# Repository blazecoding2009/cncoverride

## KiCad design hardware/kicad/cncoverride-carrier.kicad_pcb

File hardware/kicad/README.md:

# CNC Override Pendant PCB · R1

R1 replaces the harness carrier with a **190 × 170 mm direct-mount panel PCB**. The display, four knobs and eight buttons sit on the front. The ESP32-C6-DevKitC-1 and expander mount on the rear. Four Ø3.2 mm holes on a 182 × 162 mm pattern mount the main board. Dimensions and panel clearances are provisional.

| References | Direct assembly |
|---|---|
| ENC1, ENC2 | Bourns PEC11H-4215F-S0024 push encoders for Feed and Spindle. Includes plated slots for the two anchors per encoder. |
| SW1, SW2 | Lorlin CK1049, one-pole PCB rotary switch with break-before-make contacts. Set the stop washers for three and five positions respectively. |
| SW3–SW10 | 1U Cherry MX PCB-mount switches with five pins including the plastic locating pegs. Use labeled keycaps for X/Y, Z, Feed Hold and Cycle Start. |
| J1, H5–H8 | Adafruit 2050 resistive HX8357D TFT breakout, rotated to landscape. Solder a 2.54 mm header to the breakout's JP2 and to the pendant PCB. Use four M2.5 standoffs so the header carries no display mounting load. |
| J2, J3 | Solder the DevKitC's two 16-pin strips directly to the rear. The native USB-C port faces the top edge and goes to the Raspberry Pi. |
| U1 | Rear-mounted MCP23017-E/SP, 7.62 mm DIP-28. A0–A2 are grounded for address 0x20. |

## KiCad project

Open **cncoverride-carrier.kicad_pro** in KiCad 8 or later. The single-sheet schematic and PCB use the included project-local symbols and footprints. The board references are linked to their schematic instances.

## TFT connection

J1 mirrors the physical JP2 hole pattern from the Adafruit 2050 Eagle CAD. The glass faces the controls. The four TFT mounting holes use the 91.44 × 60.96 mm landscape spacing from Adafruit's CAD. Set the TFT's IM2 jumper for SPI before mounting it. Set the display rotation in firmware.

| JP2 pin | Signal |
|---|---|
| 1, 15 | GND |
| 2 | USB 5 V to VIN |
| 4 | TFT SCK |
| 6 | TFT MOSI |
| 7 | TFT CS |
| 8 | TFT D/C |
| 19 | SD CS held high by R4 |
| Other holes | Unassigned |

## Control inputs

| ESP32-C6 GPIO | Function |
|---|---|
| 0 / 1 | Feed encoder A / B |
| 2 / 3 | Spindle encoder A / B |
| 6 / 7 | Expander I²C SDA / SCL |
| 10 / 11 | Feed Hold / Cycle Start |
| 18 / 19 | Z+ / Z− |
| 20 / 21 / 22 / 23 | TFT SCK / MOSI / CS / D/C |

MCP23017 bank A bits 0–6 are X+, X−, Y+, Y−, Feed push, Spindle push, and Rapid 25%. Bank B bits 0–6 are Jog OFF, .001″, .010″, .100″, CONT, Rapid 50%, and Rapid 100%. Enable their pull-ups. GPA7 and GPB7 are reserved because the current datasheet specifies them as output only. Selector common A goes to ground. Rapid uses throws 1–3 for 25%, 50% and 100%. Jog uses throws 1–5 in the order above. In firmware, an open or ambiguous jog selector disarms jogging.

RN1 is an eight-resistor bussed 10 kΩ pull-up network with common on pin 1. R1/R2 are 4.7 kΩ for I²C, R3/R4 are 10 kΩ for expander reset and TFT SD CS. C1 is 100 nF across the expander supply. C2 is 10 µF near the TFT supply. The DevKitC's 3.3 V rail powers the expander. Its 5 V rail supplies TFT VIN. The machine's hardware E-stop uses the machine's documented circuit.

## Job buttons

- **SW9 Feed Hold (GPIO10)** requests a controlled hold. Use CNCjs gcode:pause during a running job so the sender pauses along with Grbl. Feed Hold leaves the spindle running.
- **SW10 Cycle Start (GPIO11)** starts the job already loaded in CNCjs when CNCjs and Grbl are idle. Use gcode:start for a new cycle and gcode:resume to continue a paused job when Grbl is ready. Require a fresh button press and a live controller connection. Suppress Cycle Start while Grbl is jogging, homing, alarmed, or in a door state.

The command behavior is the target for the firmware and Pi bridge. [CNCjs job commands](https://github.com/cncjs/cncjs/blob/v1.11.5/src/server/controllers/Grbl/GrblController.js#L1305-L1359) · [Grbl real-time commands](https://github.com/gnea/grbl/blob/v1.1h.20190825/doc/markdown/commands.md#grbl-v11-realtime-commands)

## Review status

All numbered schematic pins and PCB pads agree, including unused pins. The PCB placement and assigned nets are ready for routing. KiCad ERC/DRC and physical fit are pending. Check the actual TFT revision and print the hole patterns at 1:1 before fabrication. Set the enclosure depth from the TFT standoffs, rotary shoulder heights, keycap travel and USB plug clearance. Use enclosure support for knob forces and space around the Feed Hold and Cycle Start caps.

[Bourns encoder](https://www.bourns.com/docs/product-datasheets/pec11h.pdf?sfvrsn=a18340f6_5) · [Lorlin CK drilling and part numbers](https://www.electrokit.com/upload/product/41002/41002752/LorlinCK-7.pdf) · [KiCad MX drilling pattern](https://github.com/KiCad/kicad-footprints/blob/master/Button_Switch_Keyboard.pretty/SW_Cherry_MX_1.00u_PCB.kicad_mod) · [Adafruit 2050 breakout CAD](https://github.com/adafruit/3.5inch-TFT-Breakout-PCB) · [Espressif pin tables](https://docs.espressif.com/projects/esp-dev-kits/en/latest/esp32c6/esp32-c6-devkitc-1/user_guide.html#header-block) · [MCP23017 datasheet](https://ww1.microchip.com/downloads/aemDocuments/documents/APID/ProductDocuments/DataSheets/MCP23017-Data-Sheet-DS20001952.pdf)

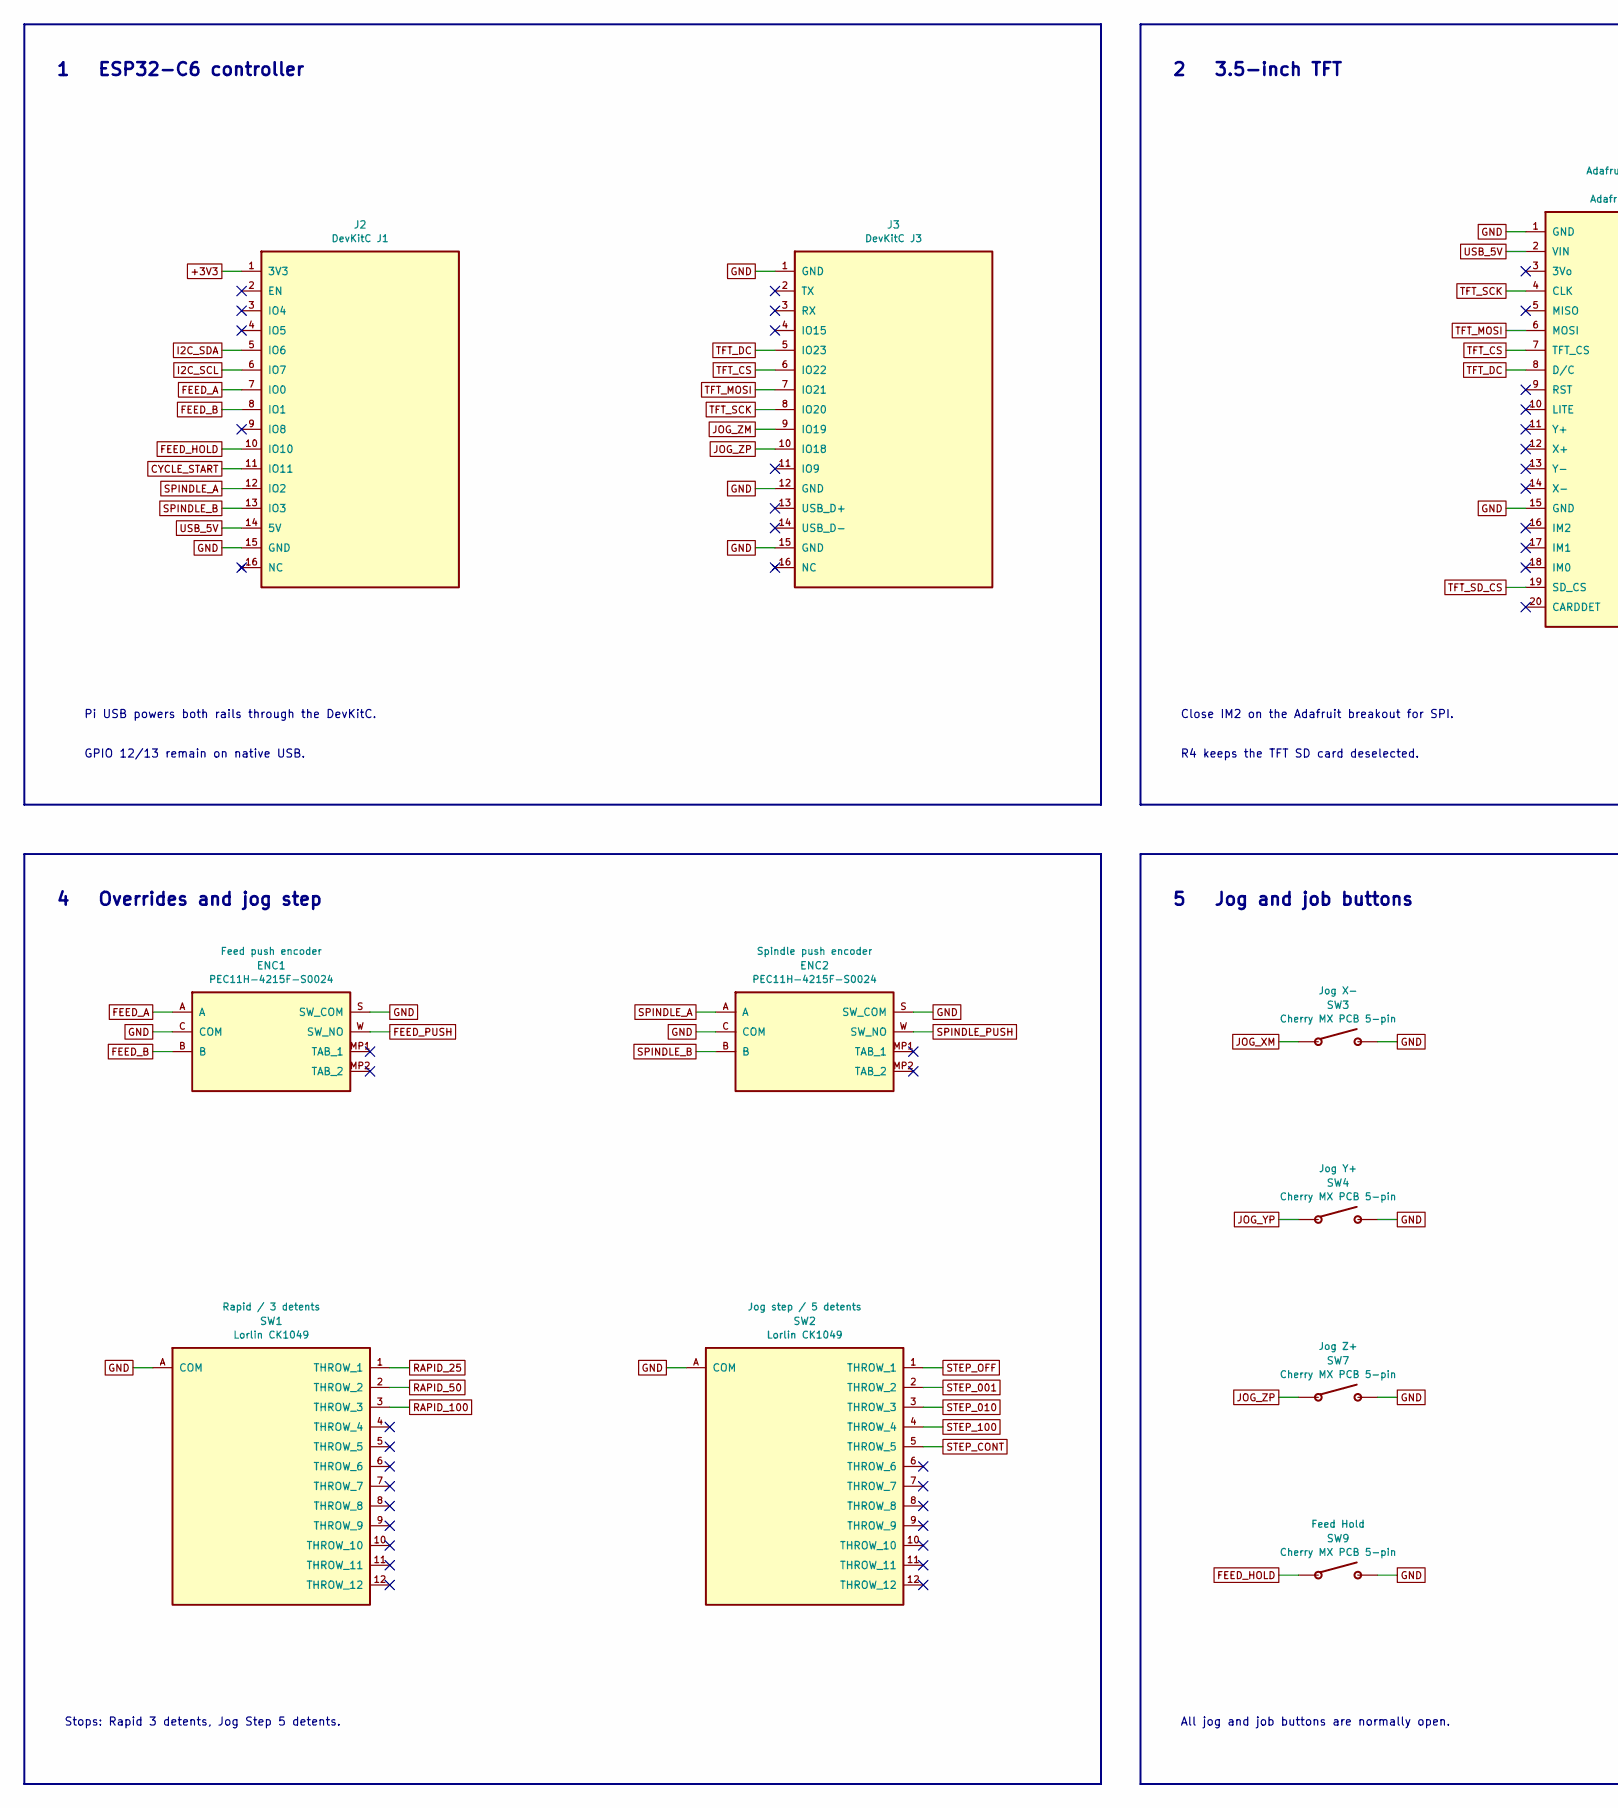
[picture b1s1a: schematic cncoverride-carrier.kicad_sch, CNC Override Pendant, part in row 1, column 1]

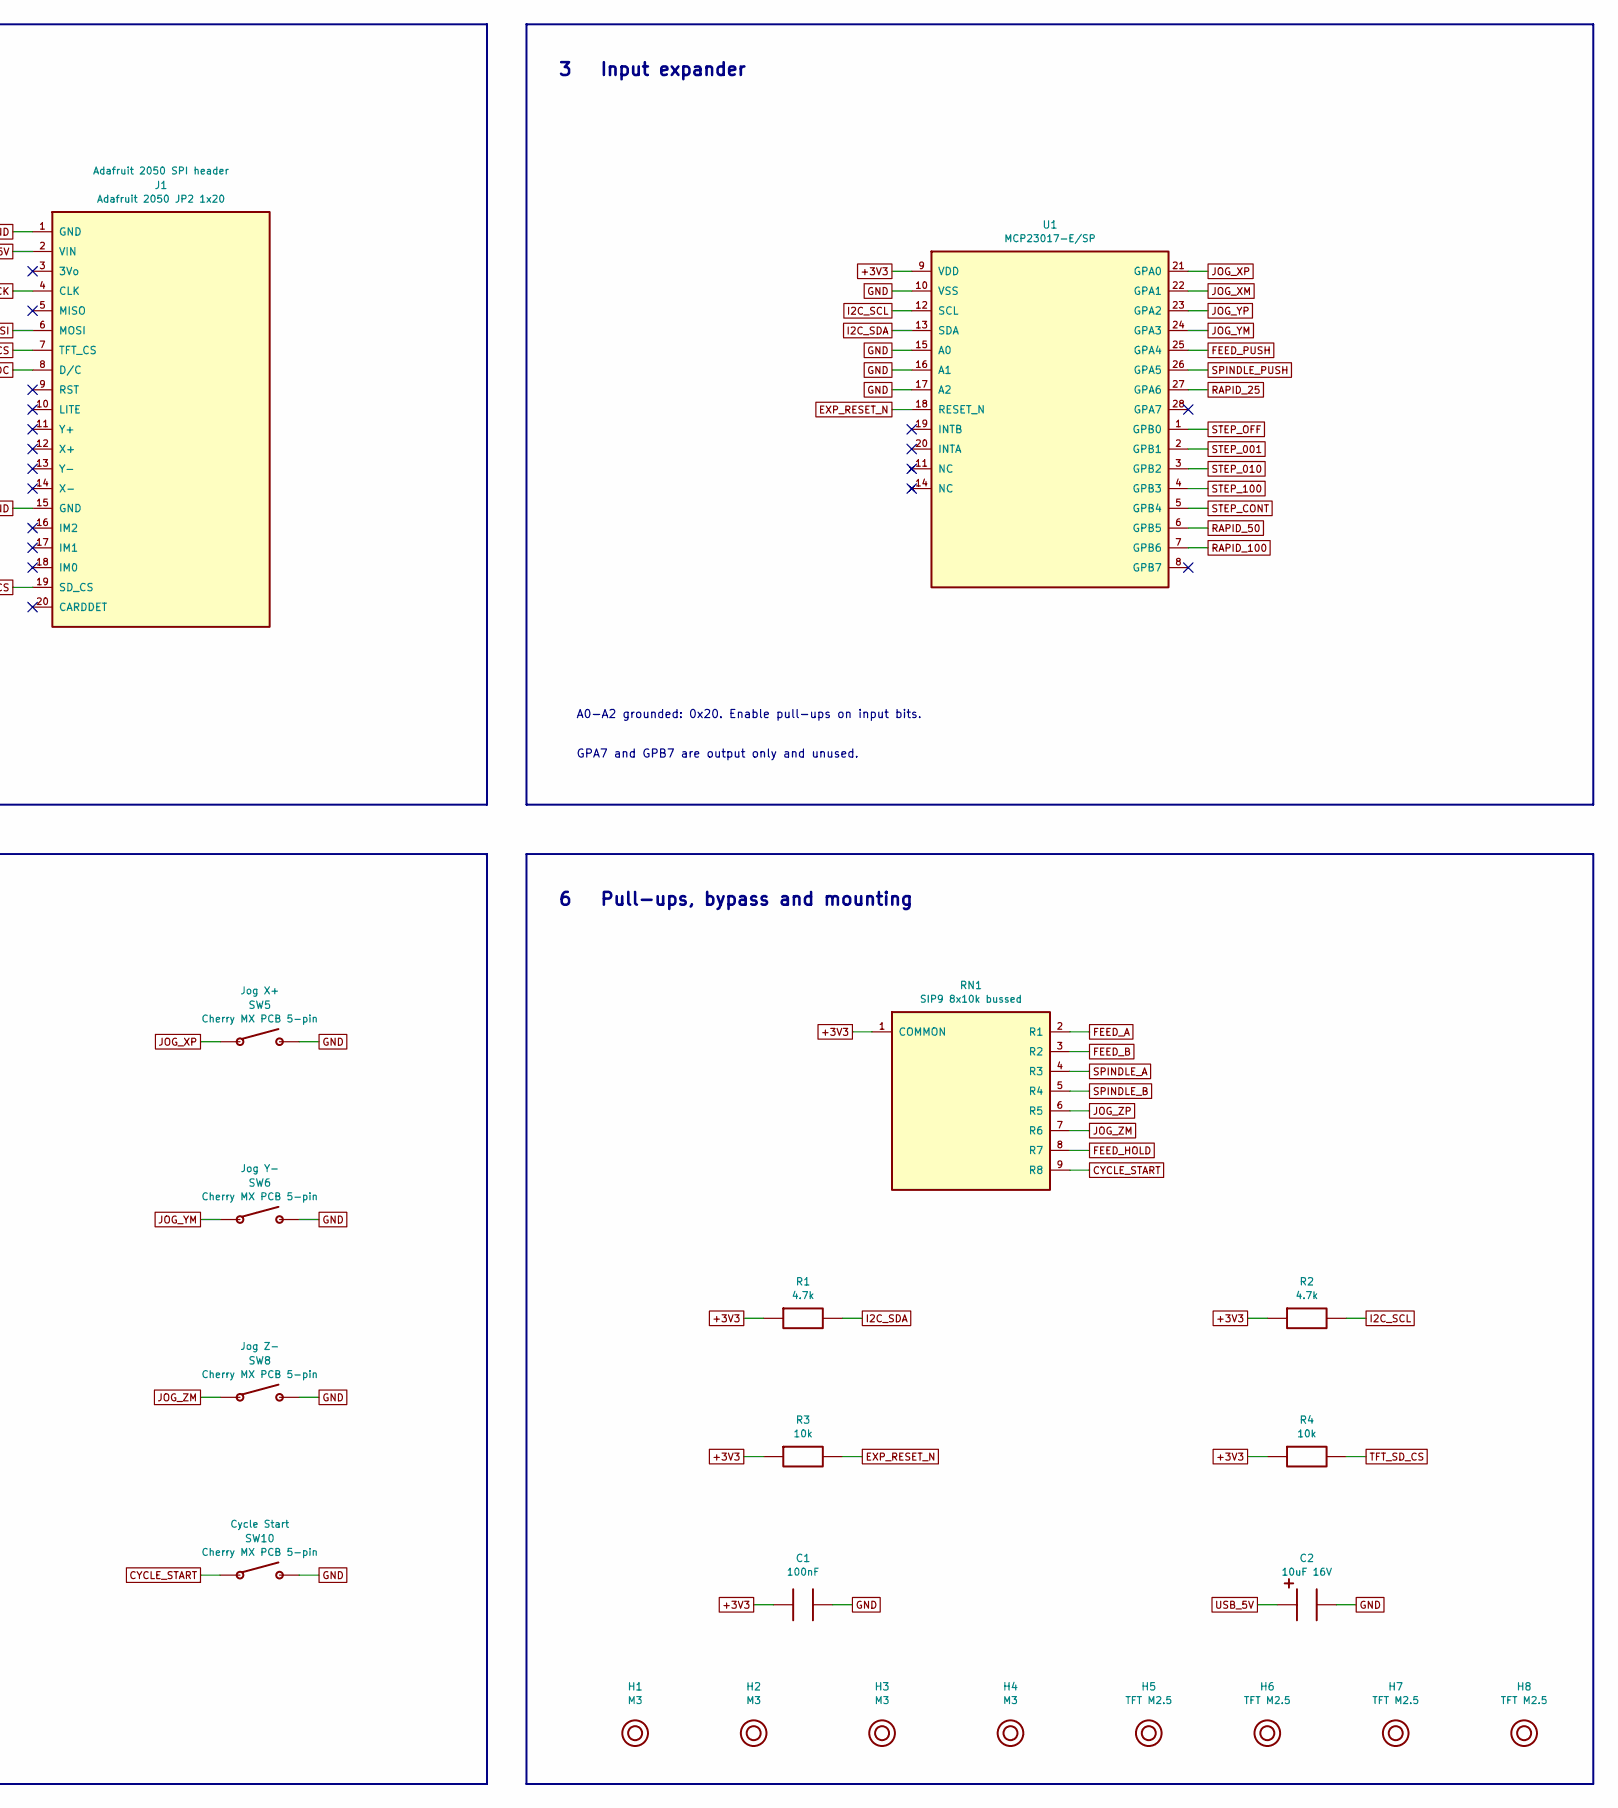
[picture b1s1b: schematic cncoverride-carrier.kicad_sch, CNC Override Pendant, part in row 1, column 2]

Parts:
C1: 100nF; C_Disc_P2.50
C2: 10uF 16V; CP_D5_P2.00
ENC1, ENC2: PEC11H-4215F-S0024; Bourns_PEC11H-S
H1, H2, H3, H4: M3; MountingHole_3.2
H5, H6, H7, H8: TFT M2.5; MountingHole_2.7
J1: Adafruit 2050 JP2 1x20; Adafruit_2050_JP2_20
J2: DevKitC J1; Header_1x16
J3: DevKitC J3; Header_1x16
R1, R2: 4.7k; R_Axial_P7.62
R3, R4: 10k; R_Axial_P7.62
RN1: SIP9 8x10k bussed; SIP9_P2.54
SW1, SW2: Lorlin CK1049; Lorlin_CK_1P12T
SW3, SW4, SW5, SW6, SW7, SW8, SW9, SW10: Cherry MX PCB 5-pin; Cherry_MX_5pin
U1: MCP23017-E/SP; DIP28_7.62

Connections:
+3V3: C1.1, J2.1 (3V3), R1.1, R2.1, R3.1, R4.1, RN1.1 (COMMON), U1.9 (VDD)
CYCLE_START: J2.11 (IO11), RN1.9 (R8), SW10.1
EXP_RESET_N: R3.2, U1.18 (RESET_N)
FEED_A: ENC1.A, J2.7 (IO0), RN1.2 (R1)
FEED_B: ENC1.B, J2.8 (IO1), RN1.3 (R2)
FEED_HOLD: J2.10 (IO10), RN1.8 (R7), SW9.1
FEED_PUSH: ENC1.W (SW_NO), U1.25 (GPA4)
GND: C1.2, C2.2, ENC1.C (COM), ENC1.S (SW_COM), ENC2.C (COM), ENC2.S (SW_COM), J1.1 (GND), J1.15 (GND), J2.15 (GND), J3.1 (GND), J3.12 (GND), J3.15 (GND), SW1.A (COM), SW2.A (COM), SW3.2, SW4.2, SW5.2, SW6.2, SW7.2, SW8.2, SW9.2, SW10.2, U1.10 (VSS), U1.15 (A0), U1.16 (A1), U1.17 (A2)
I2C_SCL: J2.6 (IO7), R2.2, U1.12 (SCL)
I2C_SDA: J2.5 (IO6), R1.2, U1.13 (SDA)
JOG_XM: SW3.1, U1.22 (GPA1)
JOG_XP: SW5.1, U1.21 (GPA0)
JOG_YM: SW6.1, U1.24 (GPA3)
JOG_YP: SW4.1, U1.23 (GPA2)
JOG_ZM: J3.9 (IO19), RN1.7 (R6), SW8.1
JOG_ZP: J3.10 (IO18), RN1.6 (R5), SW7.1
RAPID_25: SW1.1 (THROW_1), U1.27 (GPA6)
RAPID_50: SW1.2 (THROW_2), U1.6 (GPB5)
RAPID_100: SW1.3 (THROW_3), U1.7 (GPB6)
SPINDLE_A: ENC2.A, J2.12 (IO2), RN1.4 (R3)
SPINDLE_B: ENC2.B, J2.13 (IO3), RN1.5 (R4)
SPINDLE_PUSH: ENC2.W (SW_NO), U1.26 (GPA5)
STEP_001: SW2.2 (THROW_2), U1.2 (GPB1)
STEP_010: SW2.3 (THROW_3), U1.3 (GPB2)
STEP_100: SW2.4 (THROW_4), U1.4 (GPB3)
STEP_CONT: SW2.5 (THROW_5), U1.5 (GPB4)
STEP_OFF: SW2.1 (THROW_1), U1.1 (GPB0)
TFT_CS: J1.7 (TFT_CS), J3.6 (IO22)
TFT_DC: J1.8 (D/C), J3.5 (IO23)
TFT_MOSI: J1.6 (MOSI), J3.7 (IO21)
TFT_SCK: J1.4 (CLK), J3.8 (IO20)
TFT_SD_CS: J1.19 (SD_CS), R4.2
USB_5V: C2.1, J1.2 (VIN), J2.14 (5V)

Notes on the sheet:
5 Jog and job buttons
Close IM2 on the Adafruit breakout for SPI.
2 3.5-inch TFT
4 Overrides and jog step
1 ESP32-C6 controller
R4 keeps the TFT SD card deselected.
GPIO 12/13 remain on native USB.
Pi USB powers both rails through the DevKitC.
Stops: Rapid 3 detents, Jog Step 5 detents.
6 Pull-ups, bypass and mounting
All jog and job buttons are normally open.
GPA7 and GPB7 are output only and unused.
3 Input expander
A0-A2 grounded: 0x20. Enable pull-ups on input bits.

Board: 2 copper layers, 31 parts (10 on the bottom side), 33 nets, no tracks yet.
